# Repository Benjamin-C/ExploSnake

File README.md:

# ExploSnake
ExploSnake: Handheld Gaming with a Bang!

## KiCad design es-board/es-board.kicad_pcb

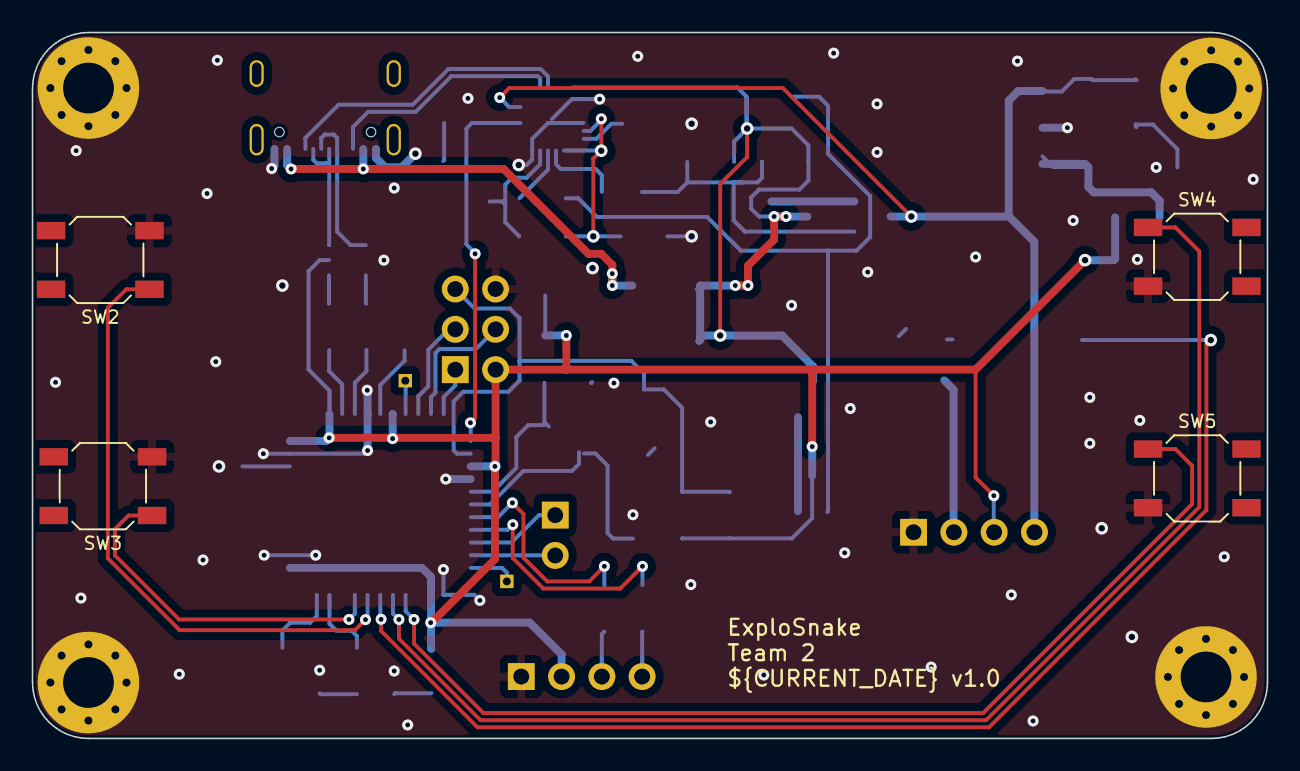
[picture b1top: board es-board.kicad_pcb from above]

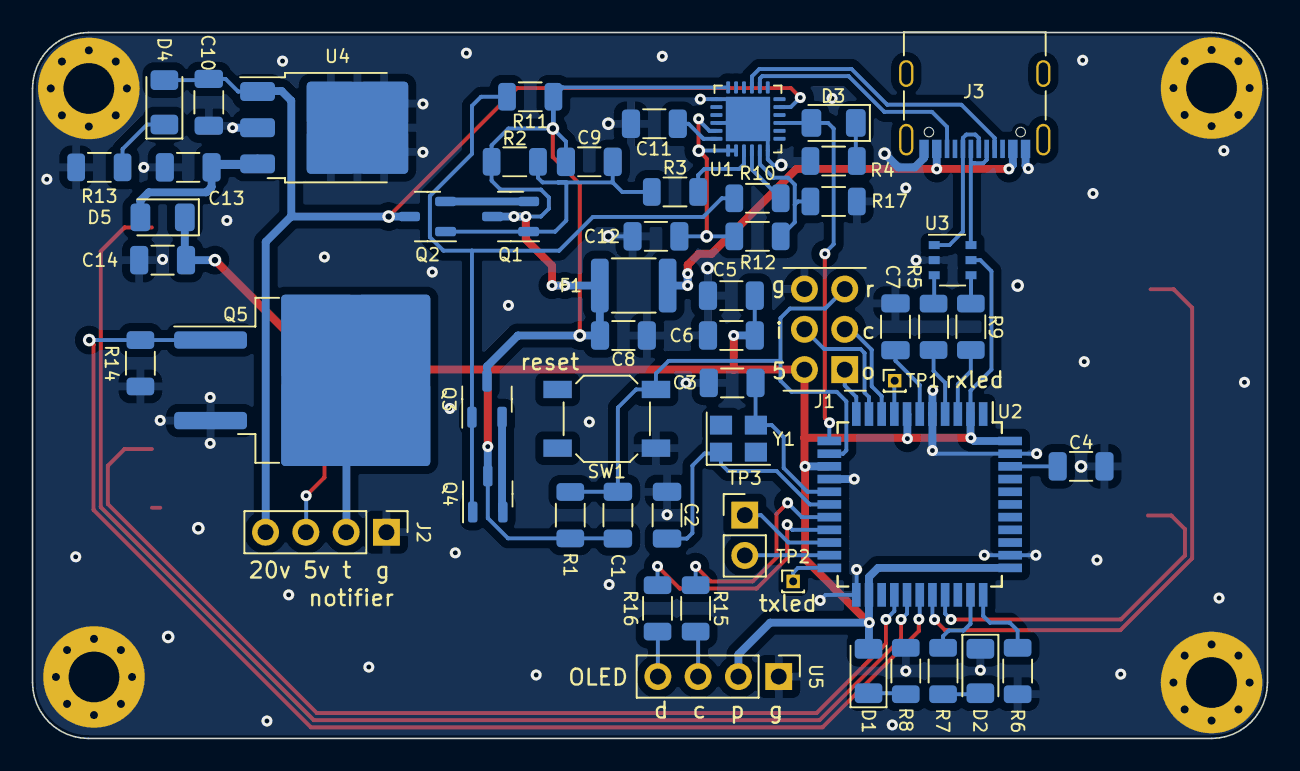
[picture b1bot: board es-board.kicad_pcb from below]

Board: 2 copper layers, 77.9 x 44.5 mm, 59 parts (55 on the bottom side), 52 nets.

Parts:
C1, C4, C7, C11, C12: 1u; C_1206_3216Metric
C2, C3: 24p; C_1206_3216Metric
C5, C6: 100n; C_1206_3216Metric
C8, C10: 10u 50V; C_1206_3216Metric
C9: 1u 50V; C_1206_3216Metric
C13: 22u; C_1206_3216Metric
C14: 100u; C_1206_3216Metric
D1, D4: green; LED_1206_3216Metric
D2: orange; LED_1206_3216Metric
D3: red; LED_1206_3216Metric
D5: D_Schottky; D_1206_3216Metric
F1: 2A; Fuse_1812_4532Metric
J1: DNP; PinHeader_2x03_P2.54mm_Vertical
J2: DNP; PinHeader_1x04_P2.54mm_Vertical
J3: USB_C_Receptacle_USB2.0; USB_C_Receptacle_Palconn_UTC16-G
Q1, Q2, Q3, Q4: Q_PMOS_GSD; SOT-23-3
Q5: IRF530NSTRLPB; TO-263-2_TabPin2
R1: 100k; R_1206_3216Metric
R2, R6, R14: 10k; R_1206_3216Metric
R3: 100; R_1206_3216Metric
R4, R17: 2k2; R_1206_3216Metric
R5, R9: 22; R_1206_3216Metric
R7, R8, R10: 1k; R_1206_3216Metric
R11: 51k; R_1206_3216Metric
R12, R13: 5k1; R_1206_3216Metric
R15, R16: 0; R_1206_3216Metric
SW1, SW2, SW3, SW4, SW5: SW_SPST; SW_SPST_SKQG_WithStem
TP1, TP2: DNP; PinHeader_1x01_P1.00mm_Vertical
TP3: DNP; PinHeader_1x02_P2.54mm_Vertical
U1: CYPD3177; QFN-24-1EP_4x4mm_P0.5mm_EP2.8x2.8mm
U2: ATmega32U4-A; TQFP-44_10x10mm_P0.8mm
U3: IP4234CZ6,125; TSOP-6_1.65x3.05mm_P0.95mm
U4: IFX25001TFV50ATMA1; TO-252-3_TabPin2
U5: OLED; PinHeader_1x04_P2.54mm_Vertical
Y1: 16MHz Crystal; Crystal_SMD_3225-4Pin_3.2x2.5mm

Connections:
+5V: C1.1, C5.1, C6.1, C14.1, D1.2 (A), D5.1 (K), J1.2, J2.3, Q4.3 (D), R1.1, U2.2 (UVCC), U2.7 (VBUS), U2.14 (VCC), U2.24 (AVCC), U2.34 (VCC), U2.44 (AVCC), U3.5 (Vbus), U5.2 (VCC)
/Digital/rx: TP3.1, U2.20 (PD2)
/Digital/tx: TP3.2, U2.21 (PD3)
/Power/3v3_usbpd: C12.1, R12.1, U1.1 (Vbus_Min), U1.2 (Vbus_Max), U1.23 (VDDD)
/Power/vbus_fused: C8.1, C9.1, F1.2, Q1.3 (D), Q3.3 (D), R2.1, R11.1, U1.18 (VBUS_IN)
DEBUG_LED: R7.1, U2.32 (PC7)
GND: C2.2, C3.2, C4.2, C5.2, C6.2, C7.2, C8.2, C10.2, C11.2, C12.2, C13.1, C14.2, D2.1 (K), J1.6, J2.1, J3.A1 (GND), J3.A12 (GND), J3.B1 (GND), J3.B12 (GND), Q5.3 (S), R4.2, R6.2, R8.2, R13.2, R14.1, R17.2, SW1.1 (A), SW2.2 (B), SW3.2 (B), SW4.2 (B), SW5.2 (B), U1.6 (Isink_Fine), U1.19 (GND), U1.22 (GND), U1.25 (PAD), U2.5 (UGND), U2.15 (GND), U2.23 (GND), U2.35 (GND), U2.43 (GND), U3.2 (gnd), U4.2 (GND), U5.1 (GND)
unnamed: D1.1 (K), R8.1
unnamed: D2.2 (A), R7.2
unnamed: D3.1 (K), R4.1
unnamed: D4.1 (K), R13.1
unnamed: C13.2, D5.2 (A), U4.3 (Vout)
unnamed: J2.2, Q5.2 (D)
unnamed: C9.2, Q1.1 (G), Q2.1 (G), R2.2, R3.2
unnamed: Q1.2 (S), Q2.2 (S)
unnamed: Q3.1 (G), Q4.1 (G), R10.1, R11.2
unnamed: Q3.2 (S), Q4.2 (S)
unnamed: R12.2, R17.1, U1.5 (Isink_Course)
unnamed: R10.2, U1.4 (Safe_Pwr_En)
unnamed: C11.1, U1.24 (VCCD)
unnamed: R3.1, U1.3 (Vbus_Fet_En)
unnamed: C4.1, U2.42 (AREF)
unnamed: R15.1, U2.18 (PD0)
unnamed: R16.1, U2.19 (PD1)
unnamed: C7.1, U2.6 (UCAP)
unnamed: C2.1, U2.17 (XTAL1), Y1.1
unnamed: C3.1, U2.16 (XTAL2), Y1.2
unnamed: R6.1, U2.33 (~HWB/PE2)
unnamed: R5.1, U3.3 (DD+)
unnamed: R9.2, U3.4 (DD-)
unnamed: J3.A6 (D+), J3.B6 (D+), U3.1 (HD+)
unnamed: J3.A7 (D-), J3.B7 (D-), U3.6 (HD-)
Reset: C1.2, J1.5, R1.2, SW1.2 (B), U2.13 (~RESET)
USB_CC1: J3.A5 (CC1), U1.15 (CC1)
USB_CC2: J3.B5 (CC2), U1.14 (CC2)
USB_D+: R5.2, U2.4 (D+)
USB_D-: R9.1, U2.3 (D-)
USB_PD_FAULT: D3.2 (A), U1.9 (FAULT), U2.12 (PB7)
VBUS: C10.1, D4.2 (A), J2.4, Q2.3 (D), U1.11 (VDC_OUT), U4.1 (Vin)
VBUS_RAW: F1.1, J3.A4 (VBUS), J3.A9 (VBUS), J3.B4 (VBUS), J3.B9 (VBUS)
btnDOWN: SW3.1 (A), U2.30 (PB6)
btnLEFT: SW4.1 (A), U2.27 (PD7)
btnRIGHT: SW5.1 (A), U2.26 (PD6)
btnUP: SW2.1 (A), U2.29 (PB5)
capboom: Q5.1 (G), R14.2, U2.28 (PB4)
miso: J1.1, U2.11 (PB3)
mosi: J1.4, U2.10 (PB2)
rxled: TP1.1, U2.8 (PB0)
sck: J1.3, U2.9 (PB1)
scl: R15.2, U5.3 (SCL)
sda: R16.2, U5.4 (SDA)
txled: TP2.1, U2.22 (PD5)

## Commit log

2023-10-19 Added PDS
2023-10-19 Created schematic
2023-10-24 Added capacitor circuit
2023-10-24 Added OLED symbol
2023-10-25 Added buttons and OLED
2023-10-25 Clean up repo
2023-10-25 Slight cleanups
2023-10-26 Added net labels for buttons
2023-11-02 Updated footprints
2023-11-02 Preliminary layout completed
2023-11-02 Created a project timeline
2023-11-02 Exported schematic and layout to PDF
2023-11-02 Exported layout to PDF
2023-11-02 Created pdfs of schematic and board layout
2023-11-02 Added pics of breadboard prototype
2023-11-04 Picked boom MOSFET
2023-11-04 Added cap boom test software
2023-11-07 Did some routing
2023-11-09 Added BOM
2023-11-09 Updated BOM format
2023-11-09 cleaned up BOM
2023-11-09 cleanup
2023-11-09 Updated board layout
2023-11-09 Individual Test Files for components
    explosnake_outline.ino is just an outline for the game.
    oled_I2C.ino is a display test for the oled display.
    push_buttons.ino is just for testing the buttons.
2023-11-15 Finished electricaling
2023-11-15 Fixed board outline and silkscreen
2023-11-16 Design review tweaks
2023-11-16 Prep for fab
2023-11-16 Added PDF of schematic and board
2023-11-16 updated BOM
2023-11-16 Set up export settings for fab and updated BOM
2023-11-29 Added build instructions v1
2023-11-29 Updated build instructions
2023-12-07 Create README for code
2023-12-07 Add all 4 version of SNAKE code
2023-12-07 Added test plan
2023-12-08 Created Documentation
    How to Play the Game
    What is the game
2023-12-08 Updated Function Decomp
    Changed the votage input from 9V to 20V.
